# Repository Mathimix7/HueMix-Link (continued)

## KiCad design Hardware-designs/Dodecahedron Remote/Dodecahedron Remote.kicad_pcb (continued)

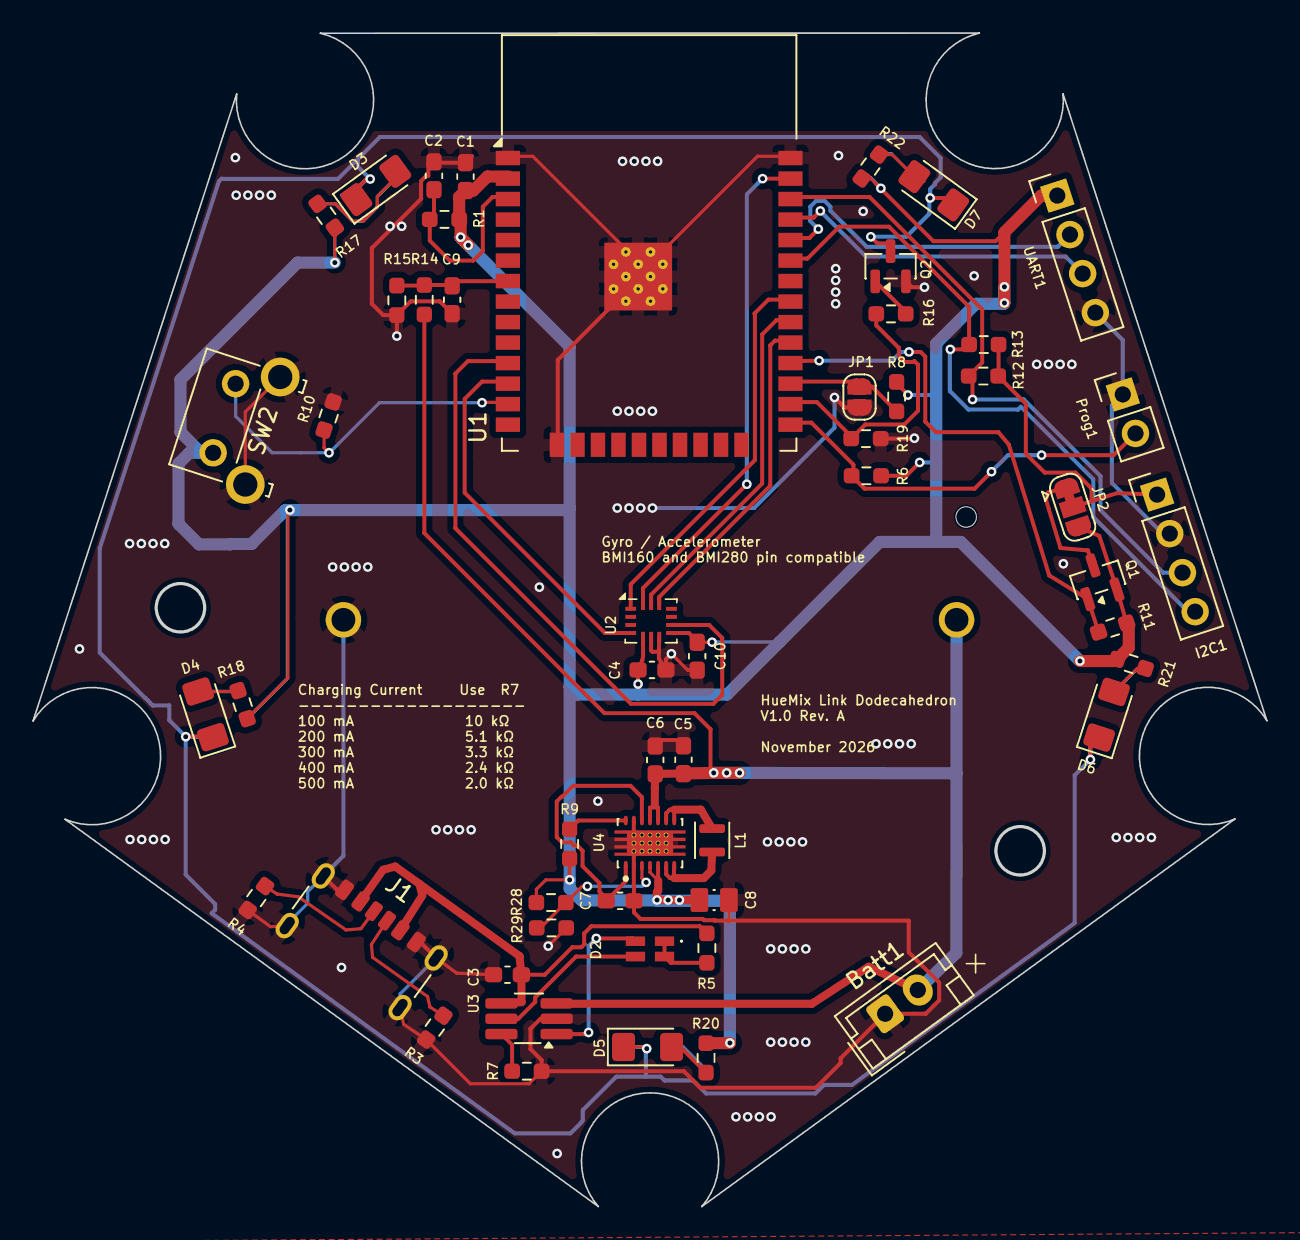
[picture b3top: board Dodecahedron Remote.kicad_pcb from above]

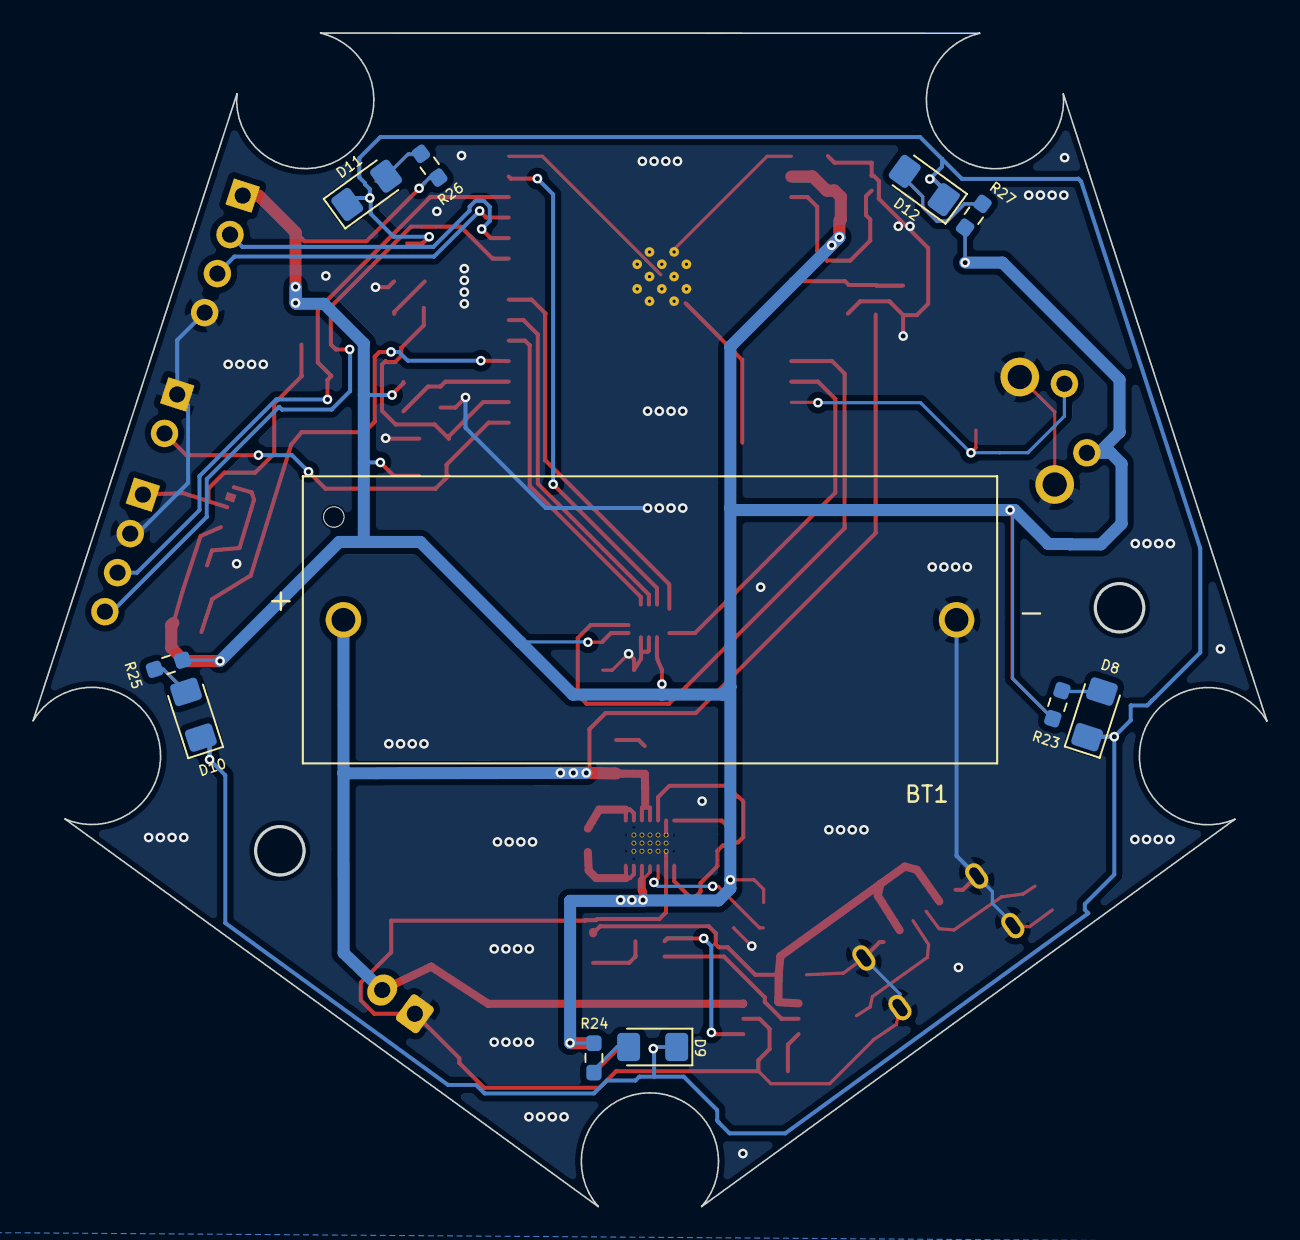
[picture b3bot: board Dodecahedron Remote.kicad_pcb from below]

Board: 2 copper layers, 76.4 x 72.7 mm, 65 parts (11 on the bottom side), 46 nets.

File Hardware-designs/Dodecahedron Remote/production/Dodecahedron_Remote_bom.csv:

Designator,Footprint,Quantity,Value,LCSC Part #
BATT1,JST_EH_B2B-EH-A_1x02_P2.50mm_Vertical,1,JST_02,
BT1,BAT_BH123A,1,BH123A,
"C1, C10, C2, C3, C4, C6, C7, C9",0603,8,100nF,
C5,0603,1,22uF,
C8,CAPC2012X145N,1,47uF,
"D10, D11, D12, D3, D4, D5, D6, D7, D8, D9",1206,10,LED,
D2,APHBM2012ETSGTC,1,Chg_Led,
I2C1,PinHeader_1x04_P2.54mm_Vertical,1,I2C,
J1,USB_C_Receptacle_GCT_USB4125-xx-x-0190_6P_TopMnt_Horizontal,1,USB_C,
L1,L_Murata_DFE201610P,1,L,
PROG1,PinHeader_1x02_P2.54mm_Vertical,1,Prog,
Q1,SOT-23,1,AO3407A,
Q2,SOT-23,1,MMBT3904,
"R1, R10, R6, R8",0603,4,10k,
"R11, R12, R13",0603,3,4.7k,
"R14, R9",0603,2,1M,
R15,0603,1,300k,
R16,0603,1,1k,
"R17, R18, R20, R21, R22, R23, R24, R25, R26, R27, R5",0603,11,330,
R19,0603,1,100k,
R28,0603,1,1.13M,
R29,0603,1,200k,
"R3, R4",0603,2,5.1k,
R7,0603,1,3.9k,
SW2,SW_SPST_Omron_B3F-315x_Angled,1,B3F-3152,
U1,ESP32-WROOM-32,1,ESP32-WROOM-32,
U2,Bosch_LGA-14_3x2.5mm_P0.5mm,1,BMI160,
U3,TSOT-23-6_HandSoldering,1,TP4057,
U4,IC_TPS63021DSJR,1,TPS63021DSJR,
UART1,PinHeader_1x04_P2.54mm_Vertical,1,UART,

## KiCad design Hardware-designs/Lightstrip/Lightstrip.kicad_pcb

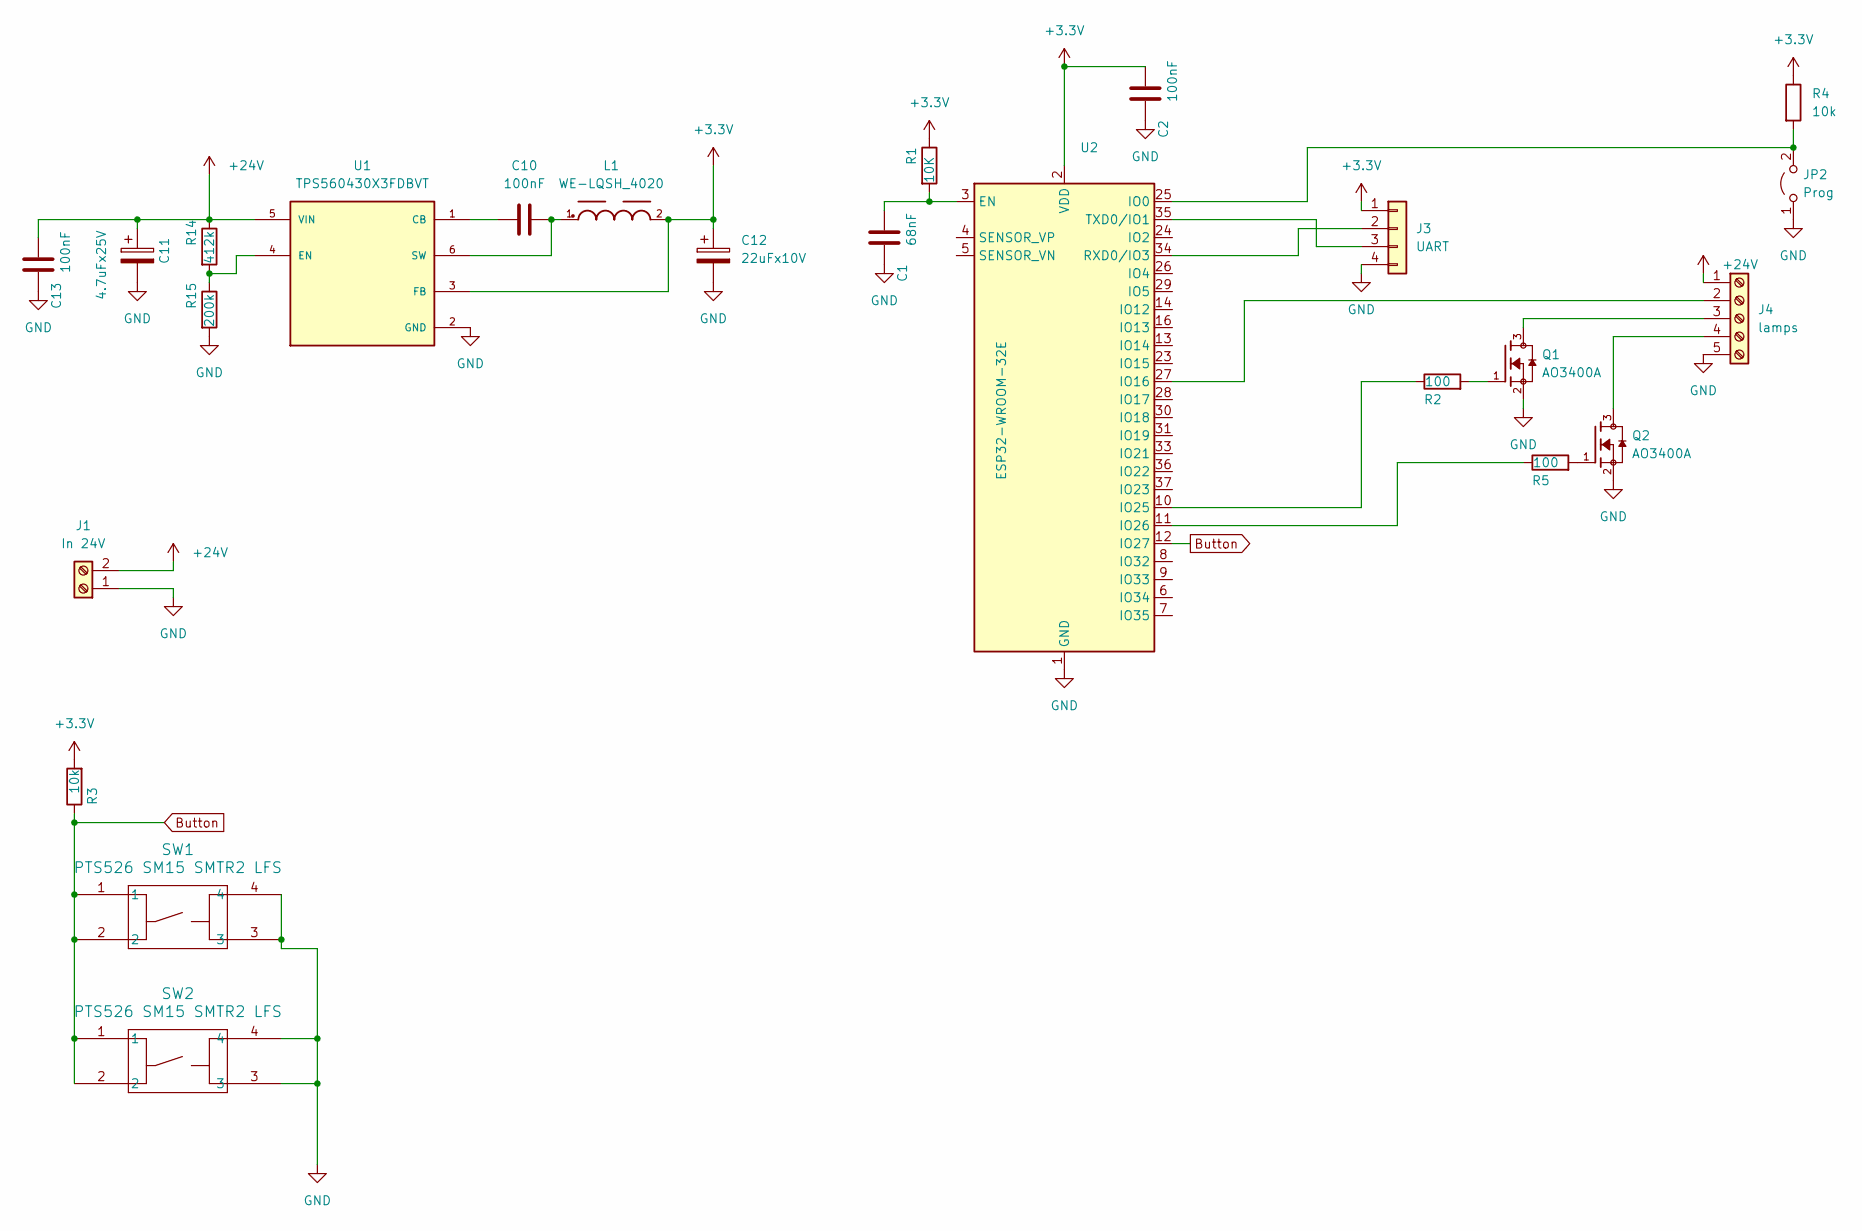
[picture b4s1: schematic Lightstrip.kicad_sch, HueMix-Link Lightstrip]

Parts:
C1: 68nF; C_0603_1608Metric_Pad1.08x0.95mm_HandSolder
C2, C10, C13: 100nF; C_0603_1608Metric_Pad1.08x0.95mm_HandSolder
C11: 4.7uFx25V; C_1206_3216Metric_Pad1.33x1.80mm_HandSolder
C12: 22uFx10V; C_1206_3216Metric_Pad1.33x1.80mm_HandSolder
J1: In 24V; TerminalBlock_MaiXu_MX126-5.0-02P_1x02_P5.00mm
J3: UART; PinHeader_1x04_P2.54mm_Vertical
J4: lamps; TerminalBlock_MaiXu_MX126-5.0-05P_1x05_P5.00mm
JP2: Prog; PinHeader_1x02_P2.54mm_Vertical
L1: WE-LQSH_4020
Q1, Q2: AO3400A; SOT95P280X125-3N; PARTREV L
R1: 10K; R_1206_3216Metric_Pad1.30x1.75mm_HandSolder
R2, R5: 100; R_1206_3216Metric_Pad1.30x1.75mm_HandSolder
R3, R4: 10k; R_1206_3216Metric_Pad1.30x1.75mm_HandSolder
R14: 412k; R_1206_3216Metric_Pad1.30x1.75mm_HandSolder
R15: 200k; R_1206_3216Metric_Pad1.30x1.75mm_HandSolder
SW1, SW2: PTS526 SM15 SMTR2 LFS; SMT_FS
U1: TPS560430X3FDBVT; IC_TPS560430X3FDBVT; PARTREV B
U2: ESP32-WROOM-32E; ESP32-WROOM-32D

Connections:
+3.3V: C2.2, C12.1, J3.1, L1.2, R1.1, R3.2, R4.1, U1.3 (FB), U2.2 (VDD)
+24V: C11.1, C13.2, J1.2, J4.1, R14.1, U1.5 (VIN)
Button: R3.1, SW1.1, SW1.2, SW2.1, SW2.2, U2.12 (IO27)
GND: C1.1, C2.1, C11.2, C12.2, C13.1, J1.1, J3.4, J4.5, JP2.1 (A), Q1.2, Q2.2, R15.2, SW1.3, SW1.4, SW2.3, SW2.4, U1.2 (GND), U2.1 (GND), U2.15 (GND), U2.38 (GND), U2.39 (GND)
unnamed: J3.2, U2.34 (RXD0/IO3)
unnamed: J3.3, U2.35 (TXD0/IO1)
unnamed: J4.2, U2.27 (IO16)
unnamed: J4.3, Q1.3
unnamed: J4.4, Q2.3
unnamed: JP2.2 (B), R4.2, U2.25 (IO0)
unnamed: Q1.1, R2.2
unnamed: Q2.1, R5.2
unnamed: C10.1, U1.1 (CB)
unnamed: R14.2, R15.1, U1.4 (EN)
unnamed: C10.2, L1.1, U1.6 (SW)
unnamed: C1.2, R1.2, U2.3 (EN)
unnamed: R2.1, U2.10 (IO25)
unnamed: R5.1, U2.11 (IO26)

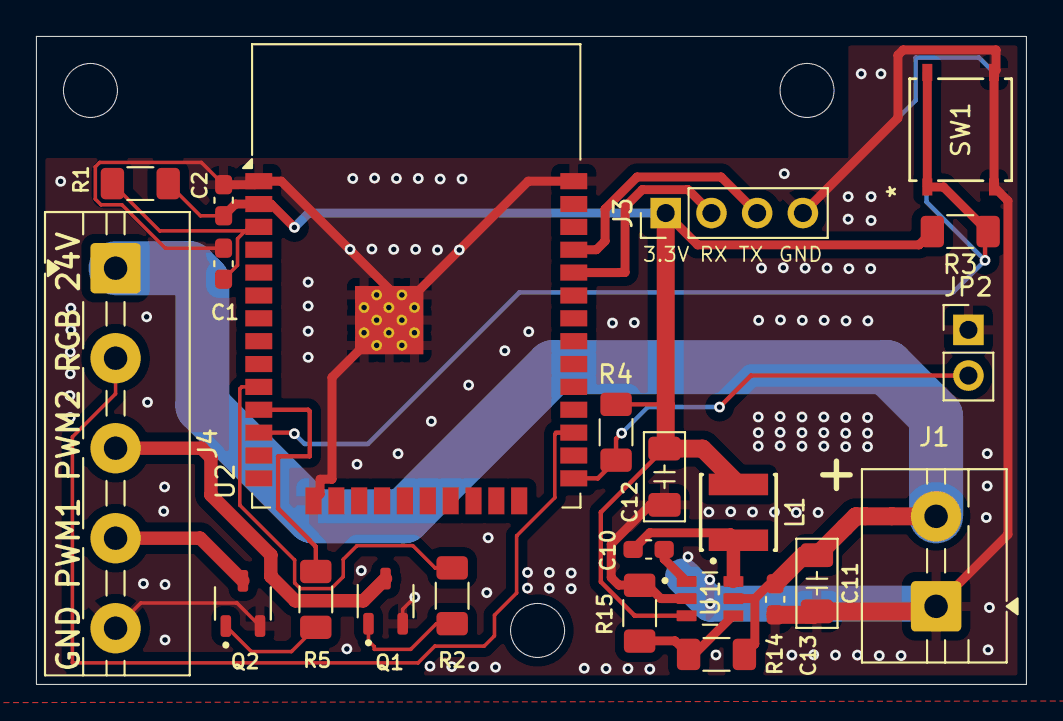
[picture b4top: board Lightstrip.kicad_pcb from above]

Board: 2 copper layers, 55.0 x 36.0 mm, 24 parts (1 on the bottom side), 18 nets.

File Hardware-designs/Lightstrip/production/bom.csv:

Designator,Footprint,Quantity,Value,LCSC Part #
C1,0603,1,68nF,
"C10, C13, C2",0603,3,100nF,
C11,1206,1,4.7uFx25V,
C12,1206,1,22uFx10V,
J1,TerminalBlock_MaiXu_MX126-5.0-02P_1x02_P5.00mm,1,In 24V,
J3,PinHeader_1x04_P2.54mm_Vertical,1,UART,
J4,TerminalBlock_MaiXu_MX126-5.0-05P_1x05_P5.00mm,1,lamps,
JP2,PinHeader_1x02_P2.54mm_Vertical,1,Prog,
L1,WE-LQSH_4020,1,WE-LQSH_4020,
"Q1, Q2",SOT95P280X125-3N,2,AO3400A,
"R1, R3, R4",1206,3,10K,
R14,1206,1,412k,
R15,1206,1,200k,
"R2, R5",1206,2,100,
"SW1, SW2",SMT_FS,2,PTS526 SM15 SMTR2 LFS,
U1,IC_TPS560430X3FDBVT,1,TPS560430X3FDBVT,
U2,ESP32-WROOM-32D,1,ESP32-WROOM-32E,

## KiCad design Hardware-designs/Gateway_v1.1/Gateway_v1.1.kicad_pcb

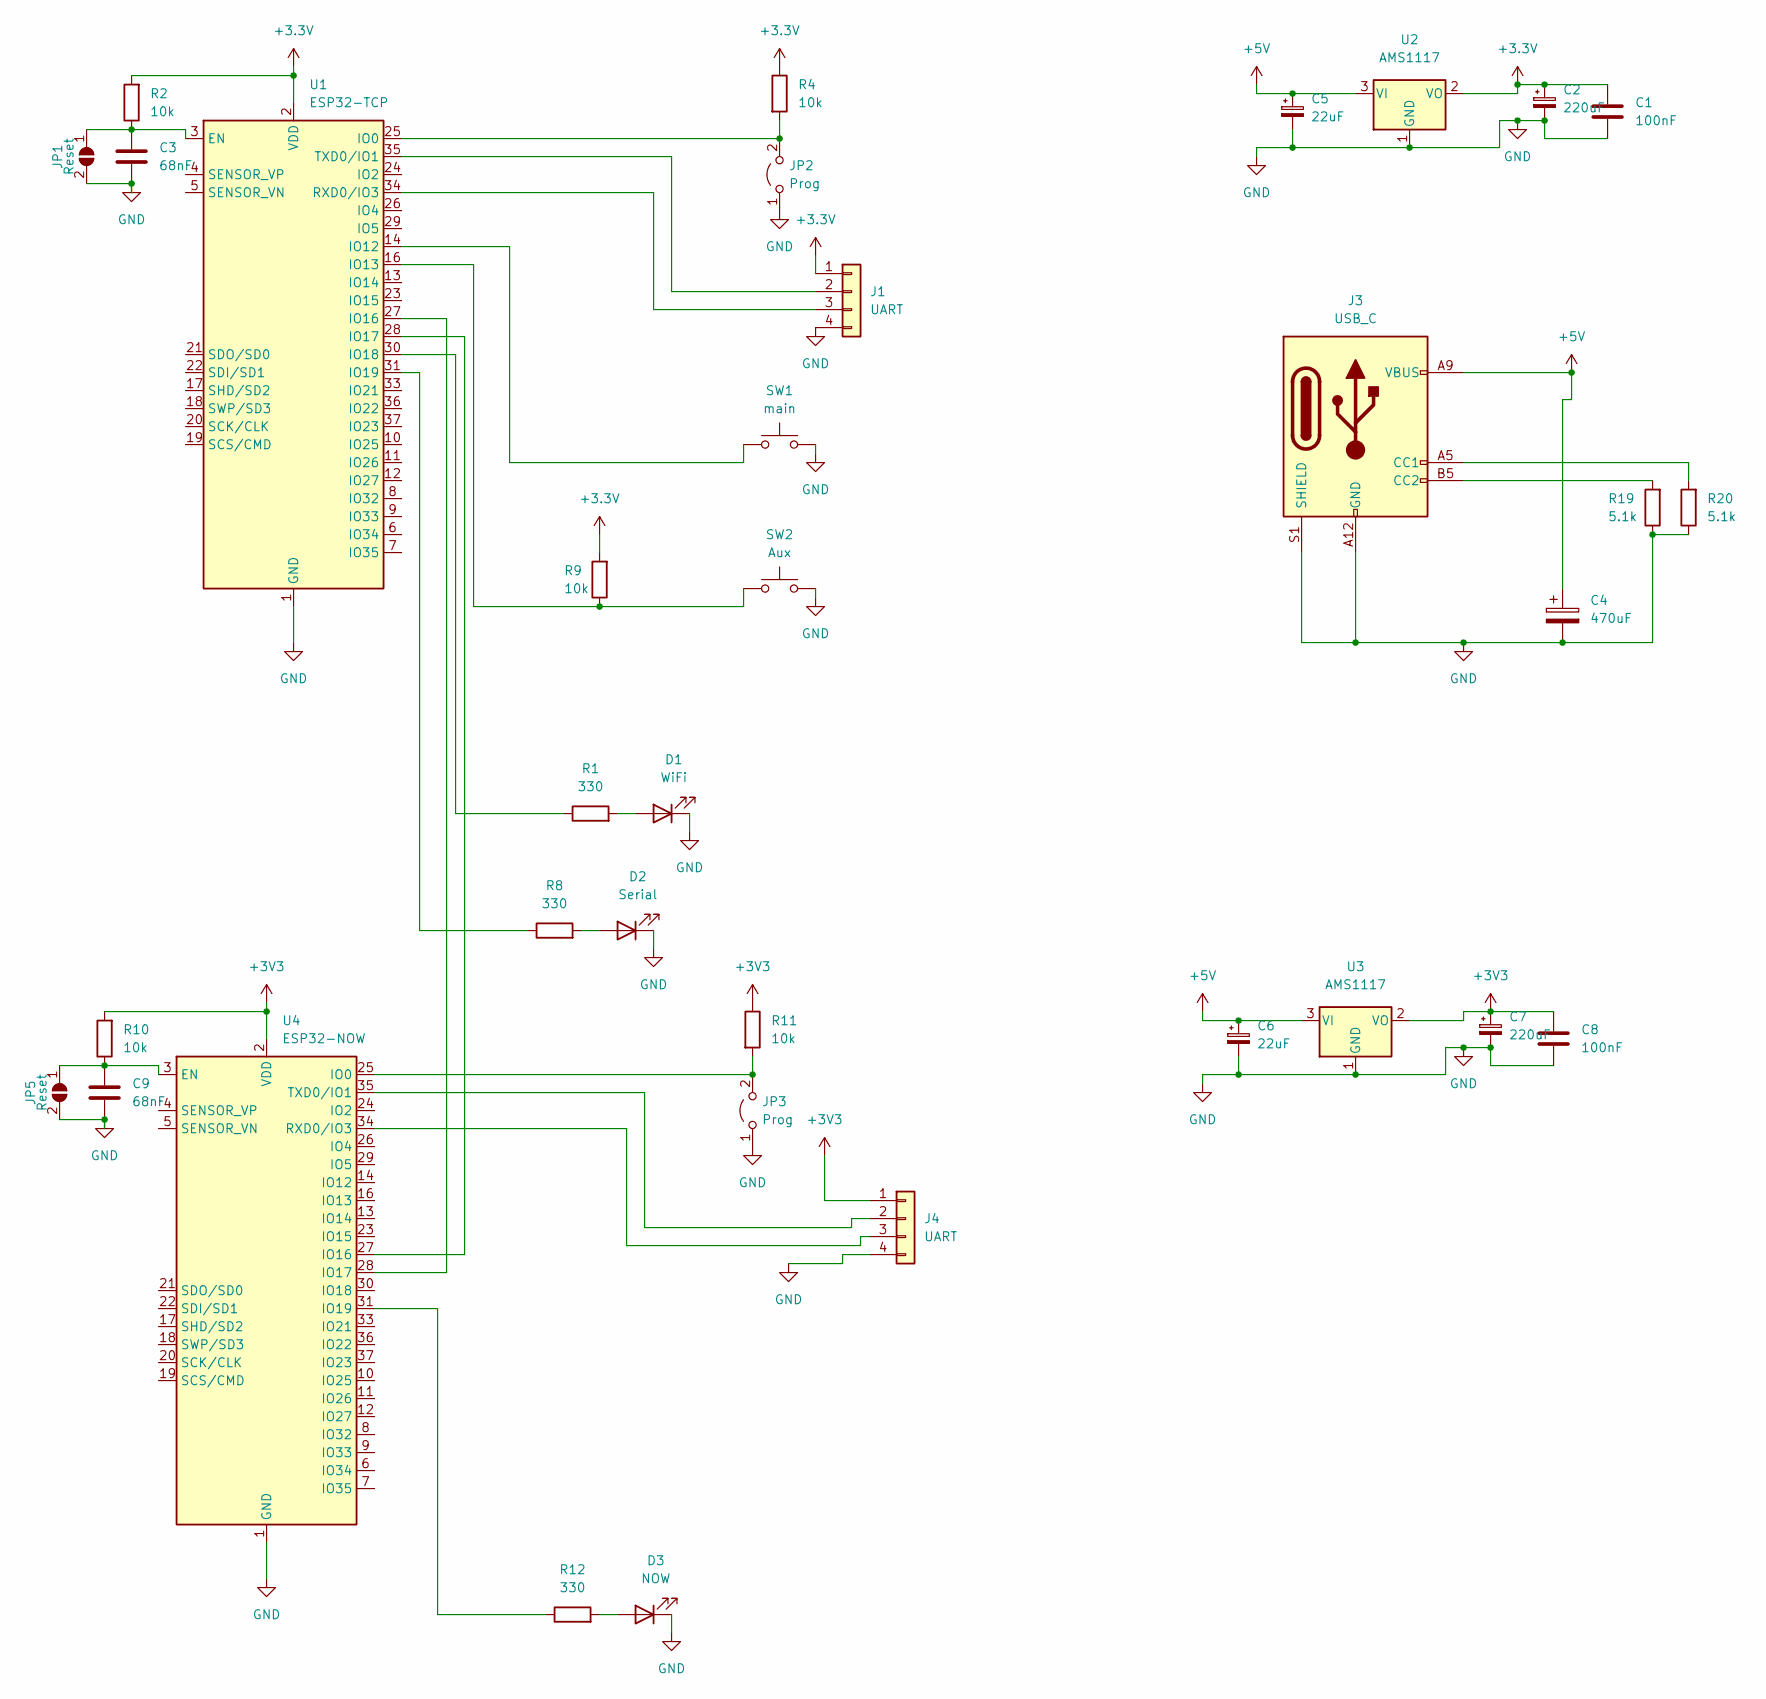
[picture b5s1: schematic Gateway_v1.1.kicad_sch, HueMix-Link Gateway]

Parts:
C1, C8: 100nF; C_0805_2012Metric_Pad1.18x1.45mm_HandSolder
C2, C7: 220uF; CP_EIA-6032-15_Kemet-U_HandSolder
C3, C9: 68nF; C_0805_2012Metric_Pad1.18x1.45mm_HandSolder
C4: 470uF; CP_Radial_D8.0mm_P3.50mm
C5, C6: 22uF; CP_EIA-6032-15_Kemet-U_HandSolder
D1: WiFi; LED_D3.0mm
D2: Serial; LED_D3.0mm
D3: NOW; LED_D3.0mm
J1, J4: UART; PinHeader_1x04_P2.54mm_Vertical
J3: USB_C; USB_C_Receptacle_GCT_USB4125-xx-x-0190_6P_TopMnt_Horizontal
JP1, JP5: Reset; SolderJumper-2_P1.3mm_Open_Pad1.0x1.5mm
JP2, JP3: Prog; PinHeader_1x02_P2.54mm_Vertical
R1, R8, R12: 330; R_1206_3216Metric_Pad1.30x1.75mm_HandSolder
R2, R4, R9, R10, R11: 10k; R_1206_3216Metric_Pad1.30x1.75mm_HandSolder
R19, R20: 5.1k; R_1206_3216Metric_Pad1.30x1.75mm_HandSolder
SW1: main; SW_PUSH-12mm
SW2: Aux; SW_PUSH_6mm
U1: ESP32-TCP; ESP32-WROOM-32
U2, U3: AMS1117; SOT-223-3_TabPin2
U4: ESP32-NOW; ESP32-WROOM-32

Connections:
+3.3V: C1.1, C2.1, J1.1, R2.2, R4.1, R9.2, U1.2 (VDD), U2.2 (VO)
+3V3: C7.1, C8.1, J4.1, R10.2, R11.1, U3.2 (VO), U4.2 (VDD)
+5V: C4.1, C5.1, C6.1, J3.A9 (VBUS), J3.B9 (VBUS), U2.3 (VI), U3.3 (VI)
GND: C1.2, C2.2, C3.2, C4.2, C5.2, C6.2, C7.2, C8.2, C9.2, D1.1 (K), D2.1 (K), D3.1 (K), J1.4, J3.A12 (GND), J3.B12 (GND), J3.S1 (SHIELD), J4.4, JP1.2 (B), JP2.1 (A), JP3.1 (A), JP5.2 (B), R19.1, R20.1, SW1.2, SW2.2, U1.1 (GND), U1.15 (GND), U1.38 (GND), U1.39 (GND), U2.1 (GND), U3.1 (GND), U4.1 (GND), U4.15 (GND), U4.38 (GND), U4.39 (GND)
unnamed: D1.2 (A), R1.2
unnamed: D2.2 (A), R8.2
unnamed: D3.2 (A), R12.2
unnamed: J1.2, U1.35 (TXD0/IO1)
unnamed: J1.3, U1.34 (RXD0/IO3)
unnamed: J3.A5 (CC1), R20.2
unnamed: J3.B5 (CC2), R19.2
unnamed: J4.2, U4.35 (TXD0/IO1)
unnamed: J4.3, U4.34 (RXD0/IO3)
unnamed: C3.1, JP1.1 (A), R2.1, U1.3 (EN)
unnamed: JP2.2 (B), R4.2, U1.25 (IO0)
unnamed: JP3.2 (B), R11.2, U4.25 (IO0)
unnamed: C9.1, JP5.1 (A), R10.1, U4.3 (EN)
unnamed: SW1.1, U1.14 (IO12)
unnamed: R9.1, SW2.1, U1.16 (IO13)
unnamed: U1.27 (IO16), U4.28 (IO17)
unnamed: U1.28 (IO17), U4.27 (IO16)
unnamed: R1.1, U1.30 (IO18)
unnamed: R8.1, U1.31 (IO19)
unnamed: R12.1, U4.31 (IO19)

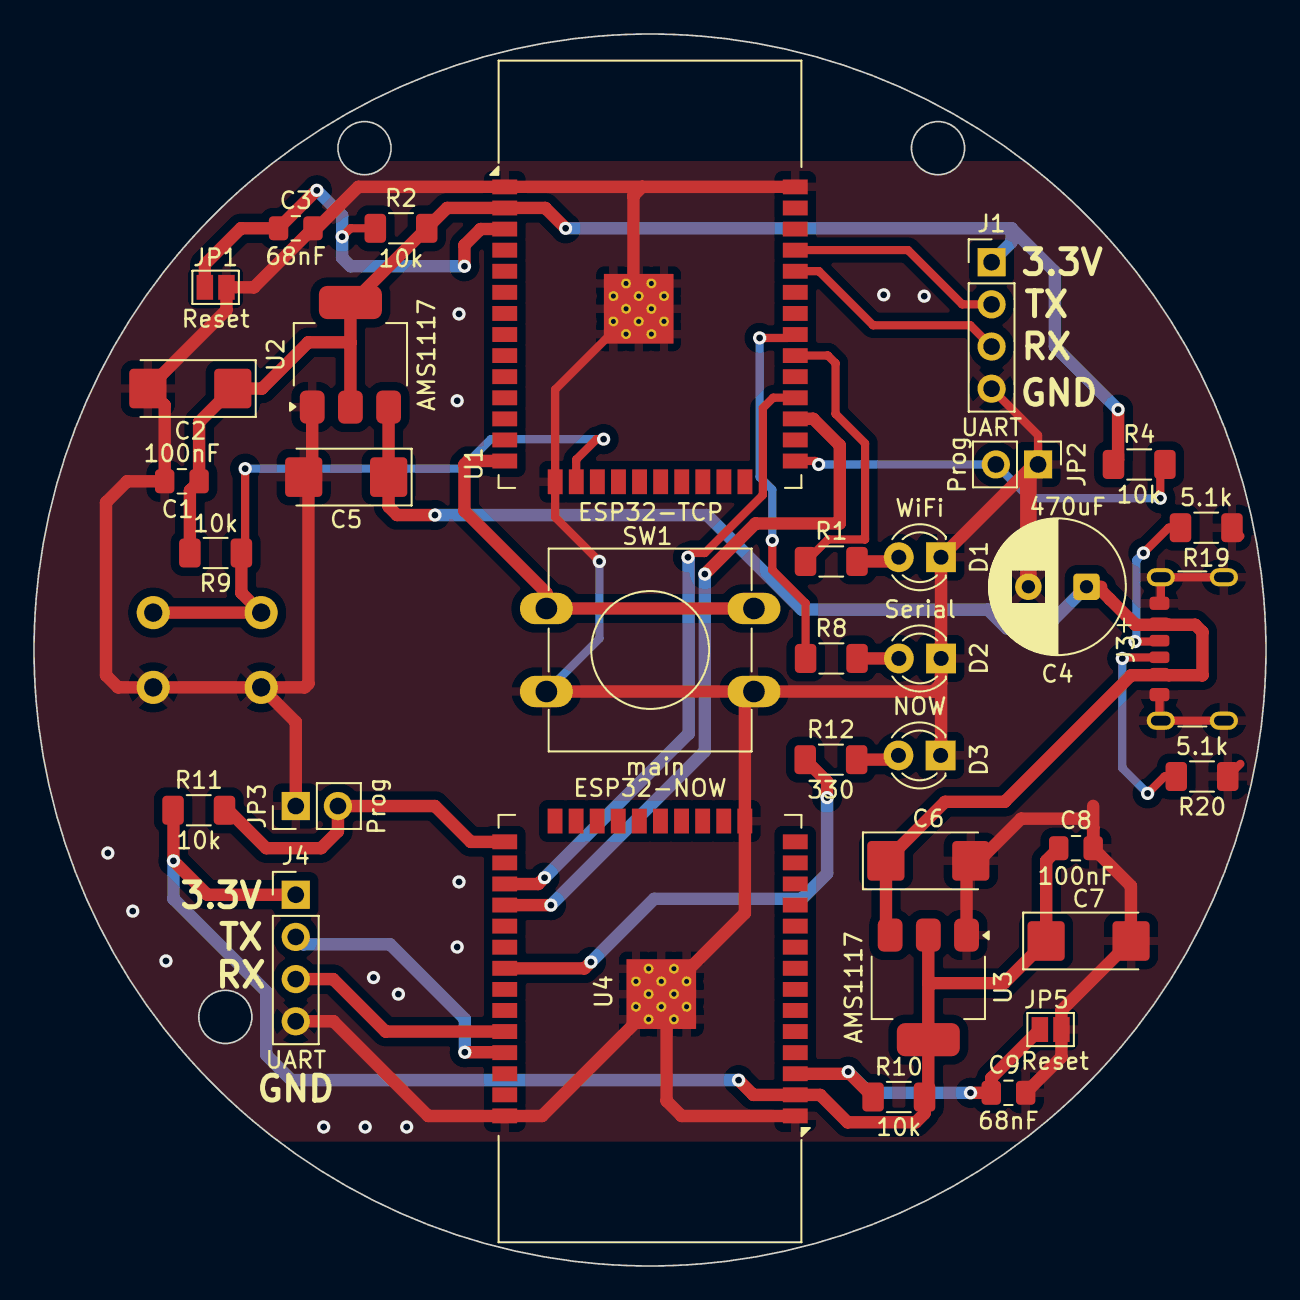
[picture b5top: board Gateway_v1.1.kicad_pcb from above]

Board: 2 copper layers, 74.2 x 74.2 mm, 35 parts (1 on the bottom side), 24 nets.

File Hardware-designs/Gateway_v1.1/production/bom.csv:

Designator,Footprint,Quantity,Value,LCSC Part #
"C1, C8",0805,2,100nF,
"C2, C7",CP_EIA-6032-15_Kemet-U_HandSolder,2,220uF,
"C3, C9",0805,2,1nF,
C4,CP_Radial_D8.0mm_P3.50mm,1,470uF,
"C5, C6",CP_EIA-6032-15_Kemet-U_HandSolder,2,22uF,
D1,LED_D3.0mm,1,WiFi,
D2,LED_D3.0mm,1,Serial,
D3,LED_D3.0mm,1,NOW,
"J1, J4",PinHeader_1x04_P2.54mm_Vertical,2,UART,
J3,USB_C_Receptacle_GCT_USB4125-xx-x-0190_6P_TopMnt_Horizontal,1,USB_C,
"JP1, JP5",SolderJumper-2_P1.3mm_Open_Pad1.0x1.5mm,2,Reset,
"JP2, JP3",PinHeader_1x02_P2.54mm_Vertical,2,Prog,
"R1, R12, R8",1206,3,330,
"R10, R11, R2, R4, R9",1206,5,10k,
"R19, R20",1206,2,5.1k,
SW1,SW_PUSH-12mm,1,main,
SW2,SW_PUSH_6mm,1,Aux,
U1,ESP32-WROOM-32,1,ESP32-TCP,
"U2, U3",SOT-223-3_TabPin2,2,AMS1117,
U4,ESP32-WROOM-32,1,ESP32-NOW,

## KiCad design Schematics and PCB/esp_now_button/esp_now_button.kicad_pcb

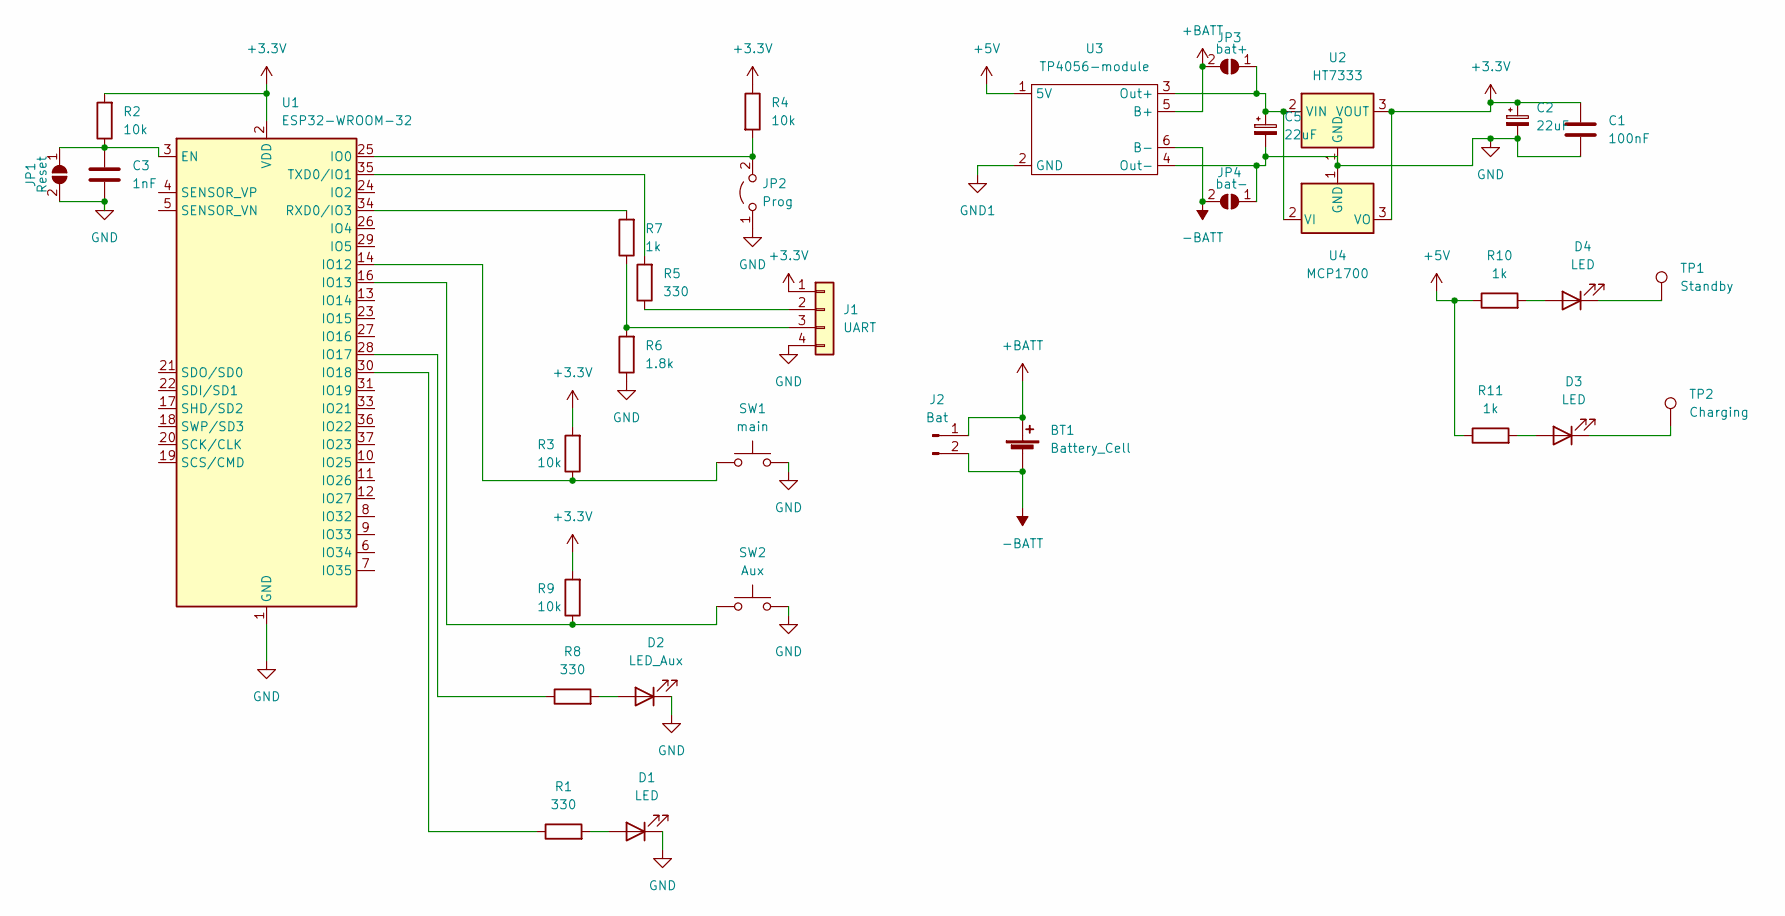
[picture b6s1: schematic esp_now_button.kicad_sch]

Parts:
BT1: Battery_Cell; BatteryHolder_ComfortableElectronic_CH273-2450_1x2450
C1: 100nF; C_0805_2012Metric_Pad1.18x1.45mm_HandSolder
C2, C5: 22uF; CP_EIA-6032-20_AVX-F_Pad2.25x2.35mm_HandSolder
C3: 1nF; C_0805_2012Metric_Pad1.18x1.45mm_HandSolder
D1, D3, D4: LED; LED_D3.0mm
D2: LED_Aux; LED_D3.0mm
J1: UART; PinHeader_1x04_P2.54mm_Vertical
J2: Bat; JST_EH_B2B-EH-A_1x02_P2.50mm_Vertical
JP1: Reset; SolderJumper-2_P1.3mm_Open_Pad1.0x1.5mm
JP2: Prog; PinHeader_1x02_P2.54mm_Vertical
JP3: bat+; SolderJumper-2_P1.3mm_Open_Pad1.0x1.5mm
JP4: bat-; SolderJumper-2_P1.3mm_Open_Pad1.0x1.5mm
R1, R5, R8: 330; R_1206_3216Metric_Pad1.30x1.75mm_HandSolder
R2, R3, R4, R9: 10k; R_1206_3216Metric_Pad1.30x1.75mm_HandSolder
R6: 1.8k; R_1206_3216Metric_Pad1.30x1.75mm_HandSolder
R7, R10, R11: 1k; R_1206_3216Metric_Pad1.30x1.75mm_HandSolder
SW1: main; SW_PUSH-12mm
SW2: Aux; SW_PUSH_6mm
TP1: Standby; TestPoint_THTPad_D1.5mm_Drill0.7mm
TP2: Charging; TestPoint_THTPad_D1.5mm_Drill0.7mm
U1: ESP32-WROOM-32
U2: HT7333; SOT-89-3
U3: TP4056-module; TP4056-18650
U4: MCP1700; TO-92_Inline

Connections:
+3.3V: C1.1, C2.1, J1.1, R2.2, R3.2, R4.1, R9.2, U1.2 (VDD), U2.3 (VOUT), U4.3 (VO)
+5V: R10.1, R11.1, U3.1 (5V)
+BATT: BT1.1 (+), J2.1, JP3.2 (B), U3.5 (B+)
-BATT: BT1.2 (-), J2.2, JP4.2 (B), U3.6 (B-)
GND: C1.2, C2.2, C3.2, C5.2, D1.1 (K), D2.1 (K), J1.4, JP1.2 (B), JP2.1 (A), JP4.1 (A), R6.1, SW1.2, SW2.2, U1.1 (GND), U1.15 (GND), U1.38 (GND), U1.39 (GND), U2.1 (GND), U3.4 (Out-), U4.1 (GND)
GND1: U3.2 (GND)
unnamed: C3.1, JP1.1 (A), R2.1, U1.3 (EN)
unnamed: C5.1, JP3.1 (A), U2.2 (VIN), U3.3 (Out+), U4.2 (VI)
unnamed: D1.2 (A), R1.2
unnamed: D2.2 (A), R8.2
unnamed: D3.1 (K), TP2.1
unnamed: D3.2 (A), R11.2
unnamed: D4.1 (K), TP1.1
unnamed: D4.2 (A), R10.2
unnamed: J1.2, R5.1
unnamed: J1.3, R6.2, R7.1
unnamed: JP2.2 (B), R4.2, U1.25 (IO0)
unnamed: R1.1, U1.30 (IO18)
unnamed: R3.1, SW1.1, U1.14 (IO12)
unnamed: R5.2, U1.35 (TXD0/IO1)
unnamed: R7.2, U1.34 (RXD0/IO3)
unnamed: R8.1, U1.28 (IO17)
unnamed: R9.1, SW2.1, U1.16 (IO13)

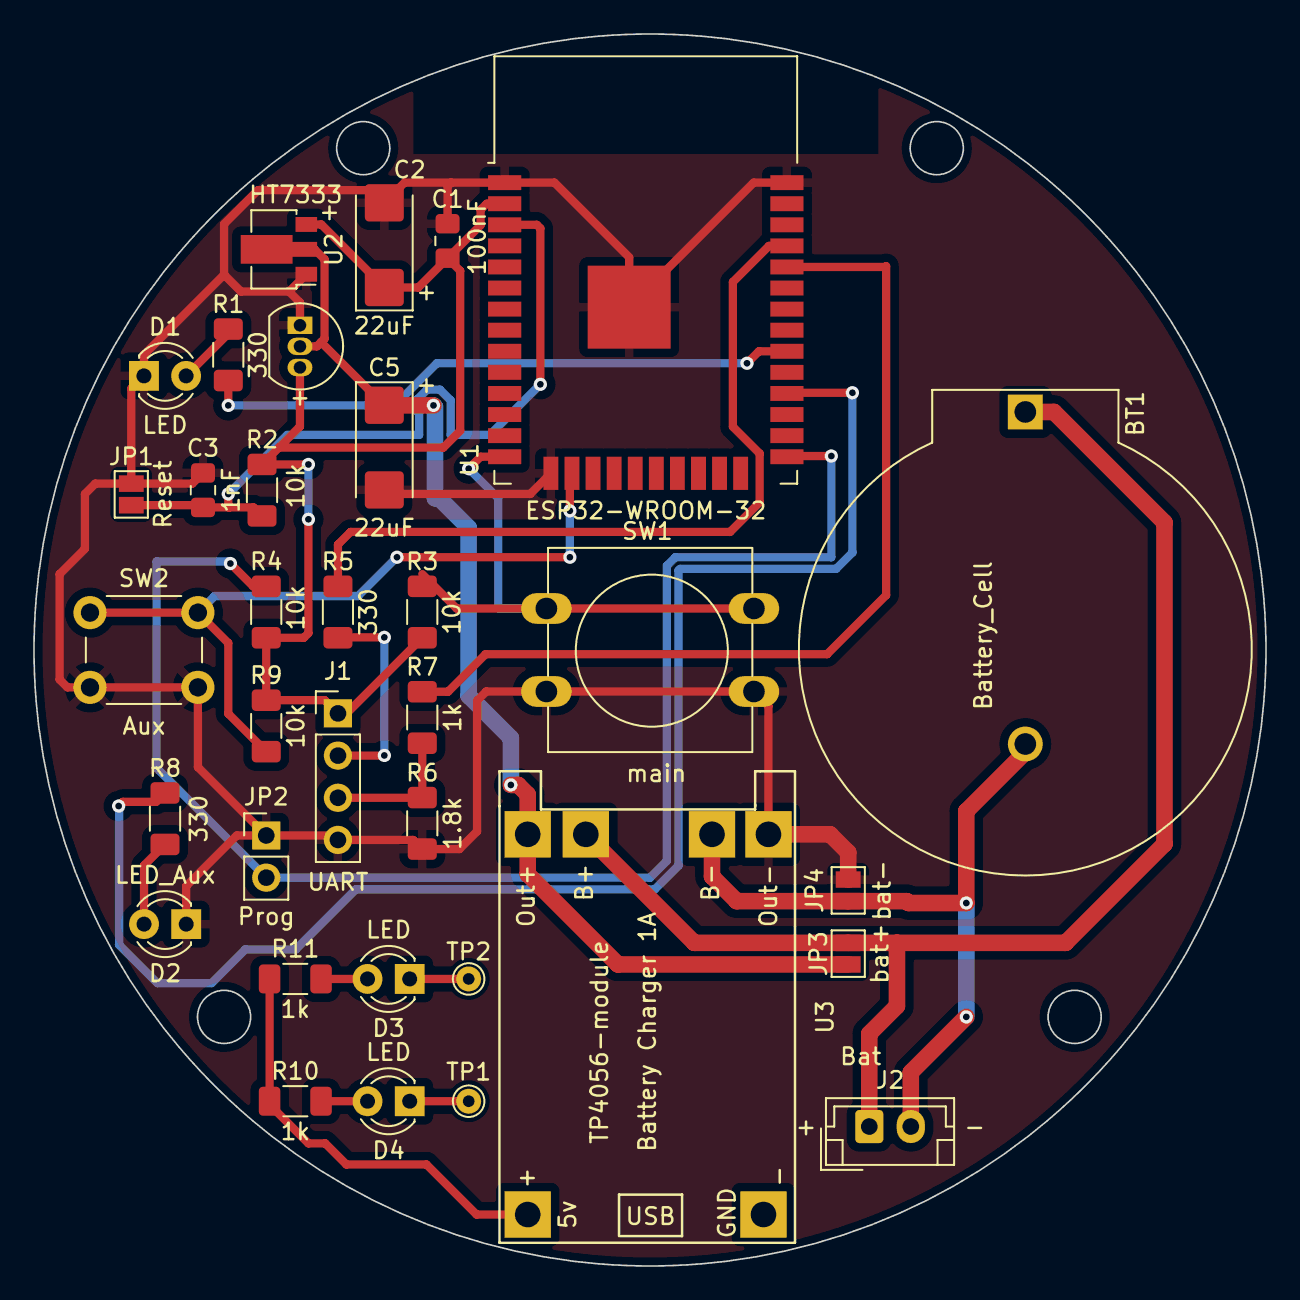
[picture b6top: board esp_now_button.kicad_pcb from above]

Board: 2 copper layers, 74.2 x 74.2 mm, 34 parts (0 on the bottom side), 22 nets.
